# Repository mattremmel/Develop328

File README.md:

# Develop328
Eagle files for a custom ATMega328P development board

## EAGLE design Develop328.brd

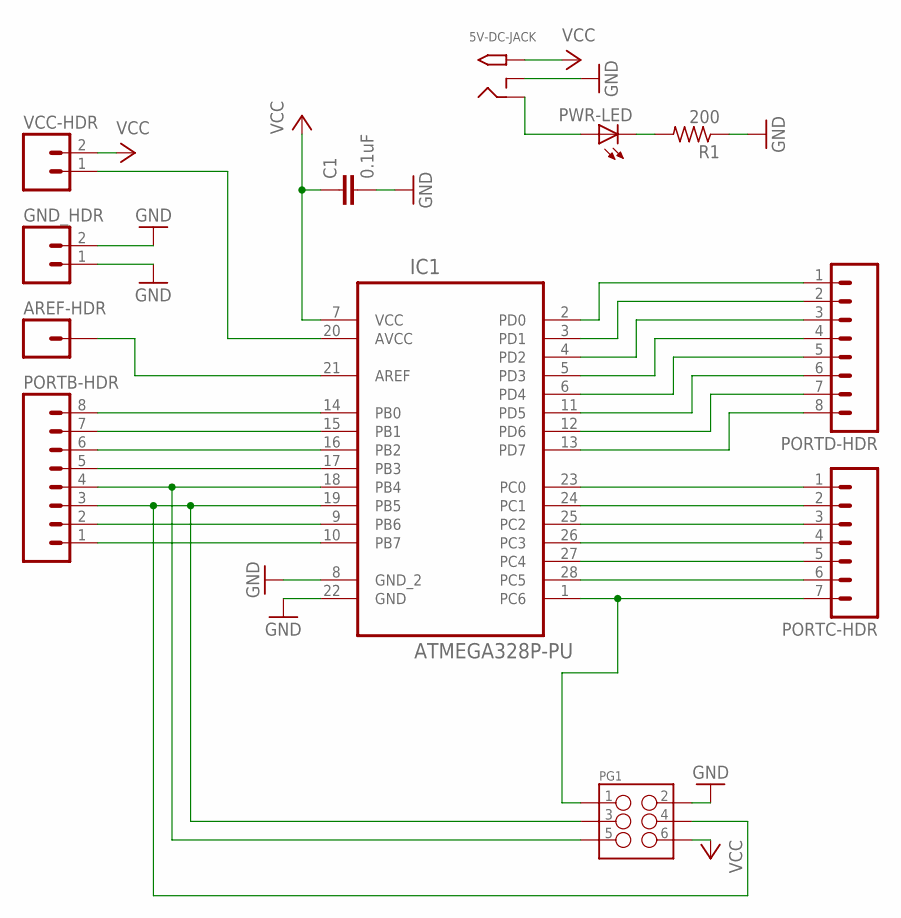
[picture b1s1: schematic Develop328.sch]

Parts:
5V-DC-JACK: 2.1MMJACKTHM; PJ-102A
AREF-HDR: M01PTH; 1X01
C1: 0.1uF; CAP-PTH-SMALL-KIT
GND_HDR: M02PTH; 1X02
IC1: ATMEGA328P-PU; DIP254P762X457-28
PG1: M03X2SHROUD; 2X3-SHROUDED
PORTB-HDR: M08; 1X08_ROUND
PORTC-HDR: M07; 1X07
PORTD-HDR: M08; 1X08_ROUND
PWR-LED: LED3MM
R1: 200; 0204/5
VCC-HDR: M02PTH; 1X02

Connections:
GND: 5V-DC-JACK.RING_SW, C1.2, GND_HDR.1, GND_HDR.2, IC1.8 (GND_2), IC1.22 (GND), PG1.2, R1.1
unnamed: IC1.14 (PB0), PORTB-HDR.8
unnamed: IC1.15 (PB1), PORTB-HDR.7
unnamed: IC1.16 (PB2), PORTB-HDR.6
unnamed: IC1.17 (PB3), PORTB-HDR.5
unnamed: IC1.18 (PB4), PG1.5, PORTB-HDR.4
unnamed: IC1.19 (PB5), PG1.3, PG1.4, PORTB-HDR.3
unnamed: IC1.9 (PB6), PORTB-HDR.2
unnamed: IC1.10 (PB7), PORTB-HDR.1
unnamed: IC1.23 (PC0), PORTC-HDR.1
unnamed: IC1.26 (PC3), PORTC-HDR.4
unnamed: IC1.27 (PC4), PORTC-HDR.5
unnamed: IC1.28 (PC5), PORTC-HDR.6
unnamed: IC1.1 (PC6), PG1.1, PORTC-HDR.7
unnamed: IC1.2 (PD0), PORTD-HDR.1
unnamed: IC1.3 (PD1), PORTD-HDR.2
unnamed: IC1.4 (PD2), PORTD-HDR.3
unnamed: IC1.5 (PD3), PORTD-HDR.4
unnamed: IC1.6 (PD4), PORTD-HDR.5
unnamed: IC1.11 (PD5), PORTD-HDR.6
unnamed: IC1.12 (PD6), PORTD-HDR.7
unnamed: IC1.13 (PD7), PORTD-HDR.8
unnamed: AREF-HDR.1, IC1.21 (AREF)
unnamed: IC1.20 (AVCC), VCC-HDR.1
unnamed: 5V-DC-JACK.RING, PWR-LED.A
unnamed: PWR-LED.K (C), R1.2
unnamed: IC1.25 (PC2), PORTC-HDR.3
unnamed: IC1.24 (PC1), PORTC-HDR.2
VCC: 5V-DC-JACK.TIP, C1.1, IC1.7 (VCC), PG1.6, VCC-HDR.2

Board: 2 copper layers, 12 parts (0 on the bottom side), 29 nets, no tracks yet.

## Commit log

2016-06-29 Adding blank project files
2016-06-29 Added first round of components to schematic
2016-06-29 Added wires to all port headers
2016-06-30 Replaced wires with electrical connections
2016-06-30 Added GND and VCC nets and wired up the 6 pin programmer
2016-07-11 Wired capacitor and led to vcc and gnd
2016-07-18 Wired up the input jack and rewired the vcc pin filter
2016-07-18 Changed capacitor out for through hole style
2016-07-18 Updated board design and laid out all parts
2016-07-18 Removed unneded ohm label from resister value
2016-07-18 Added ground plane
2016-07-18 Cleaned up and added labels to board layout
2016-07-18 Added alternative functions to pin labels
2016-07-18 Fixed incorrect wiring for 6 pin programmer
2016-07-18 Fixed incorrect labels on pcb pin headers
2016-07-18 Added name and revision labels
2016-07-18 Added author label

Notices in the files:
parts and their libraries:
SparkFun-Connectors: Licensing: Creative Commons ShareAlike 4.0 International - https://creativecommons.org/licenses/by-sa/4.0
